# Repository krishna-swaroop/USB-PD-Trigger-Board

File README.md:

# USB-PD-Trigger-Board
USB Power Delivery Sink Board based on CYPD3177

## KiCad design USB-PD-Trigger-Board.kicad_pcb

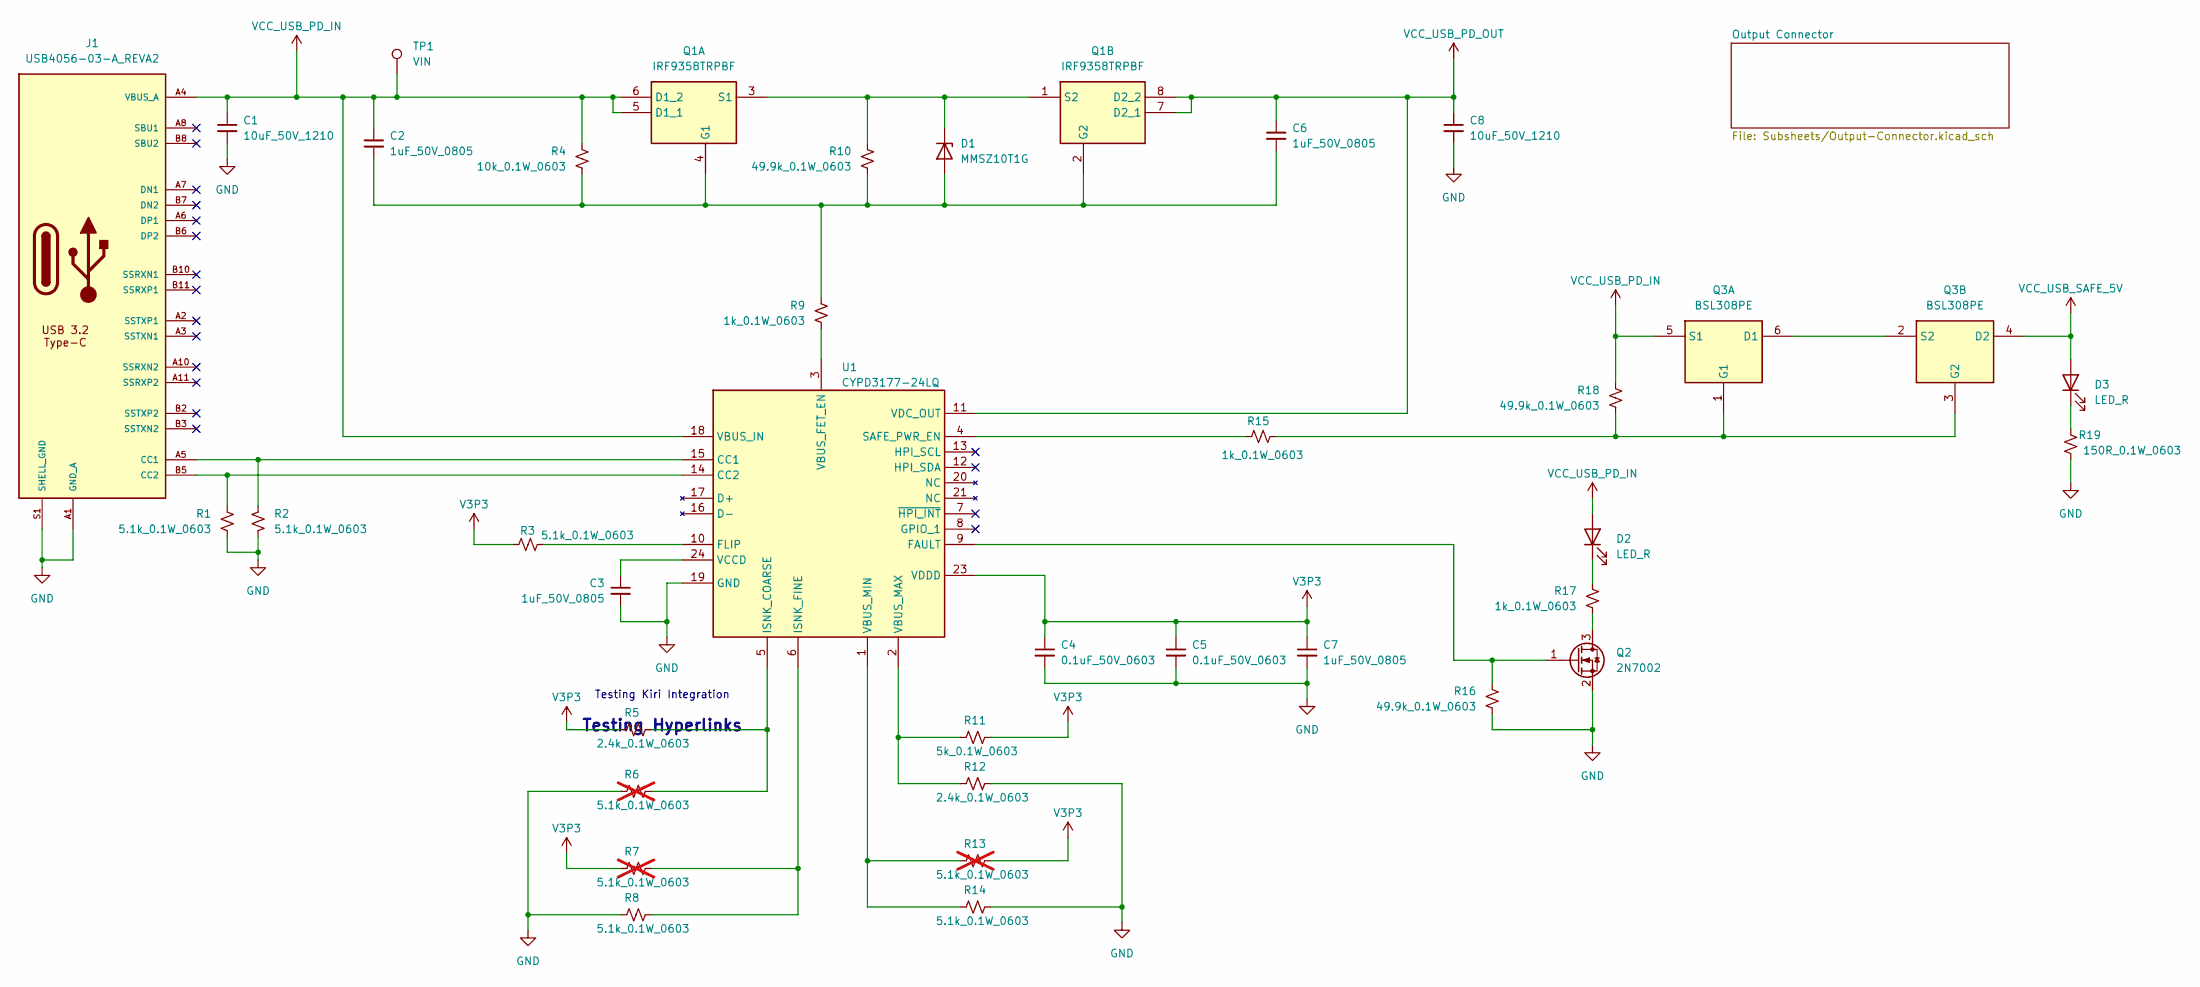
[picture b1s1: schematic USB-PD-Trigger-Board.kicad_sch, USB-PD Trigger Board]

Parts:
C1, C8: 10uF_50V_1210; C_1210_3225Metric_Pad1.33x2.70mm_HandSolder; Manufacturer Part Number CL32B106KBJNNNE
C2, C3, C6, C7: 1uF_50V_0805; C_0805_2012Metric_Pad1.18x1.45mm_HandSolder; Manufacturer Part Number CL21B105KBFNNNE
C4, C5: 0.1uF_50V_0603; C_0603_1608Metric_Pad1.08x0.95mm_HandSolder; Manufacturer Part Number C0603C104K5RACTU
D1: MMSZ10T1G; D_SOD-123; Manufacturer Part Number MMSZ10T1G
D2, D3: LED_R; D_0603_1608Metric_Pad1.05x0.95mm_HandSolder; Manufacturer Part Number SML-D12U1WT86
J1: USB4056-03-A_REVA2; USB4056-03-A; Manufacturer Part Number USB4056-03-A
Q1: IRF9358TRPBF; IRF9358TRPBFSOIC127P600X175-8N; Manufacturer_Part_Number IRF9358TRPBF; Mouser Part Number 942-IRF9358TRPBF
Q2: 2N7002; SOT-23; Manufacturer Part Number NDS7002A
Q3: BSL308PE; BSL308PE-SOT95P250X110-6N; Manufacturer_Part_Number BSL308PE; Mouser Part Number N/A
R1, R2, R3, R8, R14: 5.1k_0.1W_0603; R_0603_1608Metric_Pad0.98x0.95mm_HandSolder; Manufacturer Part Number RC0603FR-075K1L
R4: 10k_0.1W_0603; R_0603_1608Metric_Pad0.98x0.95mm_HandSolder; Manufacturer Part Number RC0603FR-0710KL
R5, R12: 2.4k_0.1W_0603; R_0603_1608Metric_Pad0.98x0.95mm_HandSolder; Manufacturer Part Number RC0603JR-072K4L
R6, R7, R13: 5.1k_0.1W_0603; R_0603_1608Metric_Pad0.98x0.95mm_HandSolder; Manufacturer Part Number RC0603FR-075K1L; not fitted
R9, R15, R17: 1k_0.1W_0603; R_0603_1608Metric_Pad0.98x0.95mm_HandSolder; Manufacturer Part Number RC0603FR-071KL
R10, R16, R18: 49.9k_0.1W_0603; R_0603_1608Metric_Pad0.98x0.95mm_HandSolder; Manufacturer Part Number RC0603FR-0749K9L
R11: 5k_0.1W_0603; R_0603_1608Metric_Pad0.98x0.95mm_HandSolder; Manufacturer Part Number RT0603BRE075KL
R19: 150R_0.1W_0603; R_0603_1608Metric_Pad0.98x0.95mm_HandSolder; Manufacturer Part Number RC0603FR-07150RL
TP1: VIN; TestPoint_Pad_D1.0mm; Manufacturer Part Number NA
U1: CYPD3177-24LQ; QFN-24-1EP_4x4mm_P0.5mm_EP2.75x2.75mm; Manufacturer Part Number CYPD3177-24LQXQT

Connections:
GND: C1.2, C3.2, C4.2, C5.2, C7.2, C8.2, J1.A1 (GND_A), J1.A12 (GND_A), J1.B1 (GND_B), J1.B12 (GND_B), J1.S1 (SHELL_GND), J1.S2 (SHELL_GND), J1.S3 (SHELL_GND), J1.S4 (SHELL_GND), Q2.2 (S), R1.2, R2.2, R6.1, R8.1, R12.2, R14.2, R16.2, R19.2, U1.19 (GND), U1.22 (GND), U1.25 (GND); also elsewhere on the board
unnamed: C2.2, C6.2, D1.2 (A), Q1.2 (G2), Q1.4 (G1), R4.2, R9.1, R10.2
unnamed: D1.1 (K), Q1.1 (S2), Q1.3 (S1), R10.1
unnamed: D2.1 (K), R17.1
unnamed: D3.1 (K), R19.1
unnamed: J1.A5 (CC1), R2.1, U1.15 (CC1)
unnamed: J1.B5 (CC2), R1.1, U1.14 (CC2)
unnamed: Q2.3 (D), R17.2
unnamed: Q2.1 (G), R16.1, U1.9 (FAULT)
unnamed: Q3.2 (S2), Q3.6 (D1)
unnamed: Q3.1 (G1), Q3.3 (G2), R15.1, R18.2
unnamed: R3.1, U1.10 (FLIP)
unnamed: R5.2, R6.2, U1.5 (ISNK_COARSE)
unnamed: R7.2, R8.2, U1.6 (ISNK_FINE)
unnamed: R15.2, U1.4 (SAFE_PWR_EN)
unnamed: R9.2, U1.3 (VBUS_FET_EN)
unnamed: R11.1, R12.1, U1.2 (VBUS_MAX)
unnamed: R13.1, R14.1, U1.1 (VBUS_MIN)
unnamed: C3.1, U1.24 (VCCD)
V3P3: C4.1, C5.1, C7.1, R3.2, R5.1, R7.1, R11.2, R13.2, U1.23 (VDDD)
VCC_USB_PD_IN: C1.1, C2.1, D2.2 (A), J1.A4 (VBUS_A), J1.A9 (VBUS_A), J1.B4 (VBUS_B), J1.B9 (VBUS_B), Q1.5 (D1_1), Q1.6 (D1_2), Q3.5 (S1), R4.1, R18.1, TP1.1, U1.18 (VBUS_IN)
VCC_USB_PD_OUT: C6.1, C8.1, Q1.7 (D2_1), Q1.8 (D2_2), U1.11 (VDC_OUT); also elsewhere on the board
VCC_USB_SAFE_5V: D3.2 (A), Q3.4 (D2)

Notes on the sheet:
Testing Kiri Integration
Testing Hyperlinks

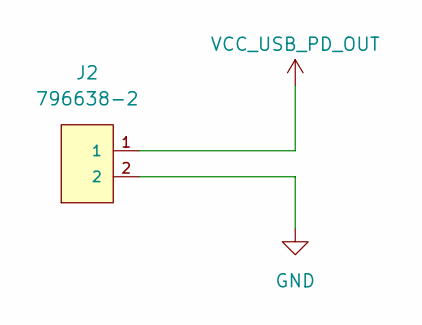
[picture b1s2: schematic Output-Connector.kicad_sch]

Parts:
J2: 796638-2

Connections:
GND: J2.2; also elsewhere on the board
VCC_USB_PD_OUT: J2.1; also elsewhere on the board

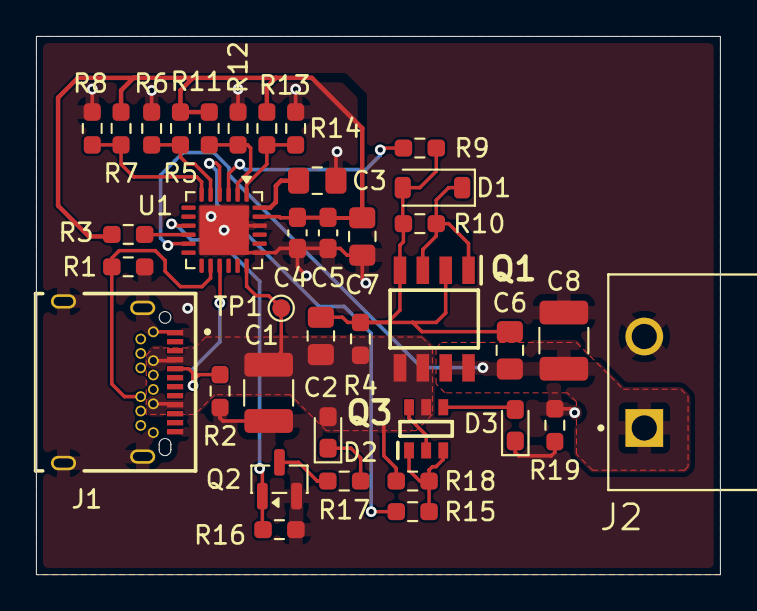
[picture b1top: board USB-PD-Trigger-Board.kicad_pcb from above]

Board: 2 copper layers, 38.0 x 29.9 mm, 37 parts (0 on the bottom side), 23 nets.

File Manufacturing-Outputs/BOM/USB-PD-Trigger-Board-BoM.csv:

"#","Qty","Reference","Value","Manufacturer_Part_Number","Footprint","Datasheet","Description","Vendor","DNP"
"1","2","C1,C8","10uF_50V_1210","","Capacitor_SMD:C_1210_3225Metric_Pad1.33x2.70mm_HandSolder","https://mm.digikey.com/Volume0/opasdata/d220001/medias/docus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","Unpolarized capacitor, small symbol","Digikey",""
"2","4","C2,C3,C6,C7","1uF_50V_0805","","Capacitor_SMD:C_0805_2012Metric_Pad1.18x1.45mm_HandSolder","https://mm.digikey.com/Volume0/opasdata/d220001/medias/docus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","Unpolarized capacitor, small symbol","Digikey",""
"3","2","C4,C5","0.1uF_50V_0603","","Capacitor_SMD:C_0603_1608Metric_Pad1.08x0.95mm_HandSolder","https://www.yageogroup.com/content/datasheet/asset/file/KEM_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","Unpolarized capacitor, small symbol","Digikey",""
"4","1","D1","MMSZ10T1G","","Diode_SMD:D_SOD-123","https://www.onsemi.com/pdf/datasheet/mmsz2v4t1-d.pdf","Zener diode","Digikey",""
"5","2","D2,D3","LED_R","","Diode_SMD:D_0603_1608Metric_Pad1.05x0.95mm_HandSolder","https://www.rohm.com/datasheet?p=SML-D12U1W&dist=Digi-key&me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","Light emitting diode","Digikey",""
"6","1","J1","USB4056-03-A_REVA2","","Pixxel_Connectors:USB4056-03-A","https://gct.co/files/specs/usb4056-spec.pdf","USB C 3.2 REC, HORZ, HYBRID PCB","Digikey",""
"7","1","J2","796638-2","","Pixxel_Connectors:796638-2","","2 Position Terminal Block Header, Male Pins, Shrouded (4 Side) 0.200"" (5.08mm) 90°, Right Angle Through Hole","",""
"8","1","Q1","IRF9358TRPBF","IRF9358TRPBF","Pixxel_MOSFETs:IRF9358TRPBFSOIC127P600X175-8N","https://www.infineon.com/dgdl/Infineon-IRF9358-DataSheet-v01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","Infineon IRF9358TRPBF Dual P-channel MOSFET, 9.2 A, 30 V HEXFET, 8-Pin SOIC","DigiKey",""
"9","1","Q2","2N7002","","Package_TO_SOT_SMD:SOT-23","https://www.onsemi.com/pub/Collateral/NDS7002A-D.PDF","0.115A Id, 60V Vds, N-Channel MOSFET, SOT-23","DigiKey",""
"10","1","Q3","BSL308PE","BSL308PE","Pixxel_MOSFETs:BSL308PE-SOT95P250X110-6N","http://uk.rs-online.com/web/p/products/8922172","Infineon BSL308PE Dual P-channel MOSFET Transistor, -2 A, -30 V, 6-Pin TSOP","DigiKey",""
"11","5","R1,R2,R3,R8,R14","5.1k_0.1W_0603","","Resistor_SMD:R_0603_1608Metric_Pad0.98x0.95mm_HandSolder","https://www.yageogroup.com/content/datasheet/asset/file/PYU-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","Resistor, small US symbol","DigiKey",""
"12","1","R4","10k_0.1W_0603","","Resistor_SMD:R_0603_1608Metric_Pad0.98x0.95mm_HandSolder","https://www.yageogroup.com/content/datasheet/asset/file/PYU-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","Resistor, small US symbol","DigiKey",""
"13","2","R5,R12","2.4k_0.1W_0603","","Resistor_SMD:R_0603_1608Metric_Pad0.98x0.95mm_HandSolder","https://www.yageogroup.com/content/datasheet/asset/file/PYU-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","Resistor, small US symbol","DigiKey",""
"14","3","R6,R7,R13","5.1k_0.1W_0603","","Resistor_SMD:R_0603_1608Metric_Pad0.98x0.95mm_HandSolder","https://www.yageogroup.com/content/datasheet/asset/file/PYU-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","Resistor, small US symbol","DigiKey","DNP"
"15","3","R9,R15,R17","1k_0.1W_0603","","Resistor_SMD:R_0603_1608Metric_Pad0.98x0.95mm_HandSolder","https://www.yageogroup.com/content/datasheet/asset/file/PYU-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","Resistor, small US symbol","DigiKey",""
"16","1","R10","50k_0.1W_0603","","Resistor_SMD:R_0603_1608Metric_Pad0.98x0.95mm_HandSolder","https://www.yageogroup.com/content/datasheet/asset/file/PYU-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","Resistor, small US symbol","DigiKey",""
"17","1","R11","5k_0.1W_0603","","Resistor_SMD:R_0603_1608Metric_Pad0.98x0.95mm_HandSolder","https://www.yageogroup.com/content/datasheet/asset/file/PYU-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","Resistor, small US symbol","DigiKey",""
"18","2","R16,R18","49.9k_0.1W_0603","","Resistor_SMD:R_0603_1608Metric_Pad0.98x0.95mm_HandSolder","https://www.yageogroup.com/content/datasheet/asset/file/PYU-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","Resistor, small US symbol","DigiKey",""
"19","1","R19","150R_0.1W_0603","","Resistor_SMD:R_0603_1608Metric_Pad0.98x0.95mm_HandSolder","https://www.yageogroup.com/content/datasheet/asset/file/PYU-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","Resistor, small US symbol","DigiKey",""
"20","1","U1","CYPD3177-24LQ","","Package_DFN_QFN:QFN-24-1EP_4x4mm_P0.5mm_EP2.75x2.75mm","https://www.infineon.com/dgdl/Infineon-EZ-PD_BCR_Datasheet_U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","Stand-alone USB PD controller (with sink Auto-run mode), QFN-24","Digikey",""

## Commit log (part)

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2026-01-21 Made a quick layout for illustrating KiCAD-Prism
2026-01-21 Added docs
2026-01-21 Adding GitHub Actions Workflows
2026-01-21 Added ibom
2026-01-21 Added 3D Model
2026-01-21 Pushing test comments for demo
2026-01-27 Testing Kiri
